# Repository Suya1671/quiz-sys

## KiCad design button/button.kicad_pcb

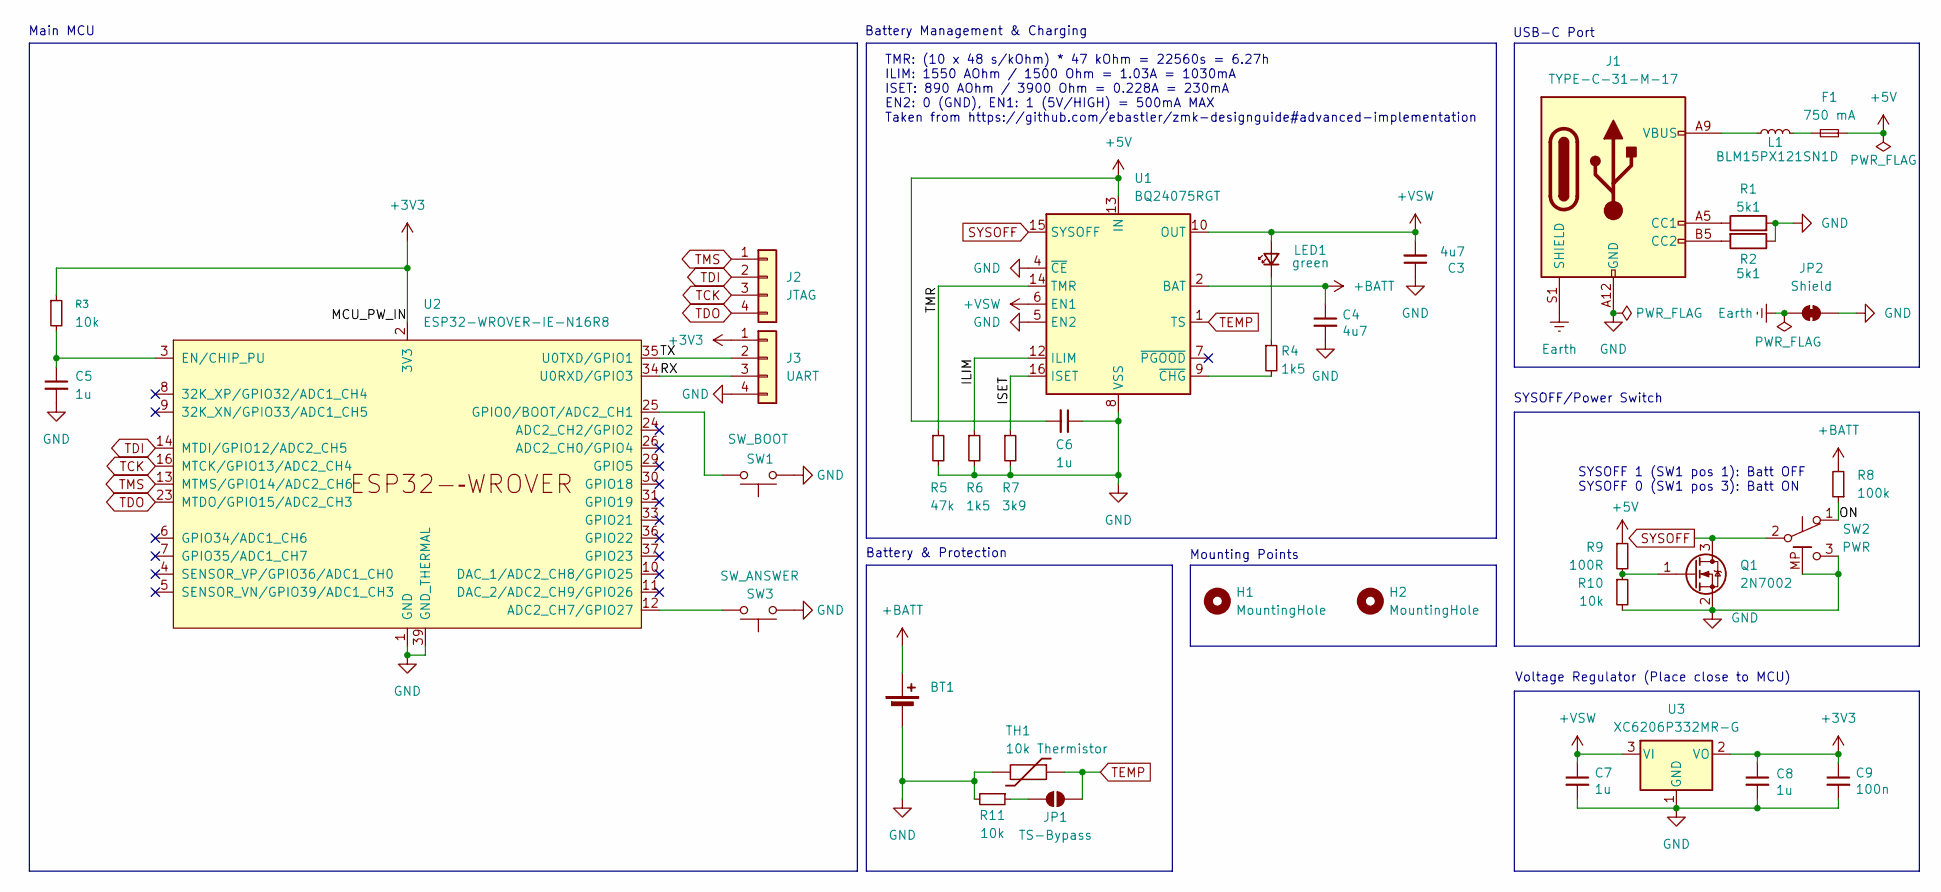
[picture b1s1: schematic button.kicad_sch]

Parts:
BT1: Battery_Cell; JST_PH_S2B-PH-K_1x02_P2.00mm_Horizontal
C3, C4: 4u7; C_0402_1005Metric_Pad0.74x0.62mm_HandSolder; LCSC C1538
C5, C6, C7, C8: 1u; C_0402_1005Metric_Pad0.74x0.62mm_HandSolder; LCSC C52923
C9: 100n; C_0402_1005Metric_Pad0.74x0.62mm_HandSolder; LCSC C1525
F1: 750 mA; Fuse_0603_1608Metric; LCSC C2687878
H1, H2: MountingHole; MountingHole_2.2mm_M2
J1: TYPE-C-31-M-17; USB_C_Receptacle_HRO_TYPE-C-31-M-17; LCSC C283540
J2: JTAG; PinHeader_1x04_P2.54mm_Horizontal; LCSC C91552
J3: UART; PinHeader_1x04_P2.54mm_Horizontal; LCSC C91552
JP1: TS-Bypass; SolderJumper-2_P1.3mm_Open_RoundedPad1.0x1.5mm
JP2: Shield; SolderJumper-2_P1.3mm_Bridged_RoundedPad1.0x1.5mm
L1: BLM15PX121SN1D; L_0402_1005Metric; LCSC C88970
LED1: green; LED_0603_1608Metric_Pad1.05x0.95mm_HandSolder; LCSC C2290
Q1: 2N7002; SOT-23; LCSC C8545
R1, R2: 5k1; R_0402_1005Metric_Pad0.72x0.64mm_HandSolder; LCSC C25905
R3, R10, R11: 10k; R_0402_1005Metric_Pad0.72x0.64mm_HandSolder; LCSC C25744
R4, R6: 1k5; R_0402_1005Metric_Pad0.72x0.64mm_HandSolder; LCSC C25867
R5: 47k; R_0402_1005Metric_Pad0.72x0.64mm_HandSolder; LCSC C25792
R7: 3k9; R_0603_1608Metric_Pad0.98x0.95mm_HandSolder; LCSC C23018
R8: 100k; R_0402_1005Metric_Pad0.72x0.64mm_HandSolder; LCSC C25741
R9: 100R; R_0402_1005Metric_Pad0.72x0.64mm_HandSolder; LCSC C25076
SW1: SW_BOOT; TS-1088-AR02016; LCSC C720477
SW2: PWR; SW_MSK12C02-HB; LCSC C431541
SW3: SW_ANSWER; WAGO 2060-452998-404; LCSC C2765055
TH1: 10k Thermistor; TestPoint_2Pads_Pitch5.08mm_Drill1.3mm
U1: BQ24075RGT; VQFN-16-1EP_3x3mm_P0.5mm_EP1.6x1.6mm; LCSC C15464
U2: ESP32-WROVER-IE-N16R8; ESP32-WROVER-E
U3: XC6206P332MR-G; SOT-23-3; LCSC C5446

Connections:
+3V3: C8.1, C9.1, J3.1, R3.1, U2.2 (3V3), U3.2 (VO)
+5V: C6.2, F1.2, R9.1, U1.13 (IN)
+BATT: BT1.1 (+), C4.1, R8.2, U1.2 (BAT), U1.3 (BAT)
+VSW: C3.2, C7.1, LED1.2 (A), U1.6 (EN1), U1.10 (OUT), U1.11 (OUT), U3.3 (VI)
/ILIM: R6.1, U1.12 (ILIM)
/ISET: R7.1, U1.16 (ISET)
/ON: R8.1, SW2.1 (A)
/RX: J3.3, U2.34 (U0RXD/GPIO3)
/TMR: R5.1, U1.14 (TMR)
/TX: J3.2, U2.35 (U0TXD/GPIO1)
Earth: J1.S1 (SHIELD), JP2.1 (A)
GND: BT1.2 (-), C3.1, C4.2, C5.2, C6.1, C7.2, C8.2, C9.2, J1.A12 (GND), J1.B12 (GND), J3.4, JP2.2 (B), Q1.2 (S), R1.2, R2.1, R5.2, R6.2, R7.2, R10.2, R11.2, SW1.1, SW2.3 (C), SW2.MP (Mounting), SW3.1, TH1.2, U1.4 (~CE), U1.5 (EN2), U1.8 (VSS), U1.17 (VSS), U2.1 (GND), U2.15 (GND), U2.38 (GND), U2.39 (GND_THERMAL), U3.1 (GND)
unnamed: F1.1, L1.2
unnamed: J1.A5 (CC1), R1.1
unnamed: J1.B5 (CC2), R2.2
unnamed: J1.A9 (VBUS), J1.B9 (VBUS), L1.1
unnamed: JP1.1 (A), R11.1
unnamed: LED1.1 (K), R4.1
unnamed: Q1.1 (G), R9.2, R10.1
unnamed: R4.2, U1.9 (~CHG)
unnamed: SW3.2, U2.12 (ADC2_CH7/GPIO27)
unnamed: C5.1, R3.2, U2.3 (EN/CHIP_PU)
unnamed: SW1.2, U2.25 (GPIO0/BOOT/ADC2_CH1)
SYSOFF: Q1.3 (D), SW2.2 (B), U1.15 (SYSOFF)
TCK: J2.3, U2.16 (MTCK/GPIO13/ADC2_CH4)
TDI: J2.2, U2.14 (MTDI/GPIO12/ADC2_CH5)
TDO: J2.4, U2.23 (MTDO/GPIO15/ADC2_CH3)
TEMP: JP1.2 (B), TH1.1, U1.1 (TS)
TMS: J2.1, U2.13 (MTMS/GPIO14/ADC2_CH6)

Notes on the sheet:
Mounting Points
USB-C Port
TMR: (10 x 48 s/kOhm) * 47 kOhm = 22560s = 6.27h ILIM: 1550 AOhm / 1500 Ohm = 1.03A = 1030mA ISET: 890 AOhm / 3900 Ohm = 0.228A = 230mA EN2: 0 (GND), EN1: 1 (5V/HIGH) = 500mA MAX Taken from https://github.com/ebastler/zmk-designguide#advanced-implementation
Battery Management & Charging
SYSOFF/Power Switch
Voltage Regulator (Place close to MCU)
Main MCU
SYSOFF 1 (SW1 pos 1): Batt OFF SYSOFF 0 (SW1 pos 3): Batt ON
Battery & Protection

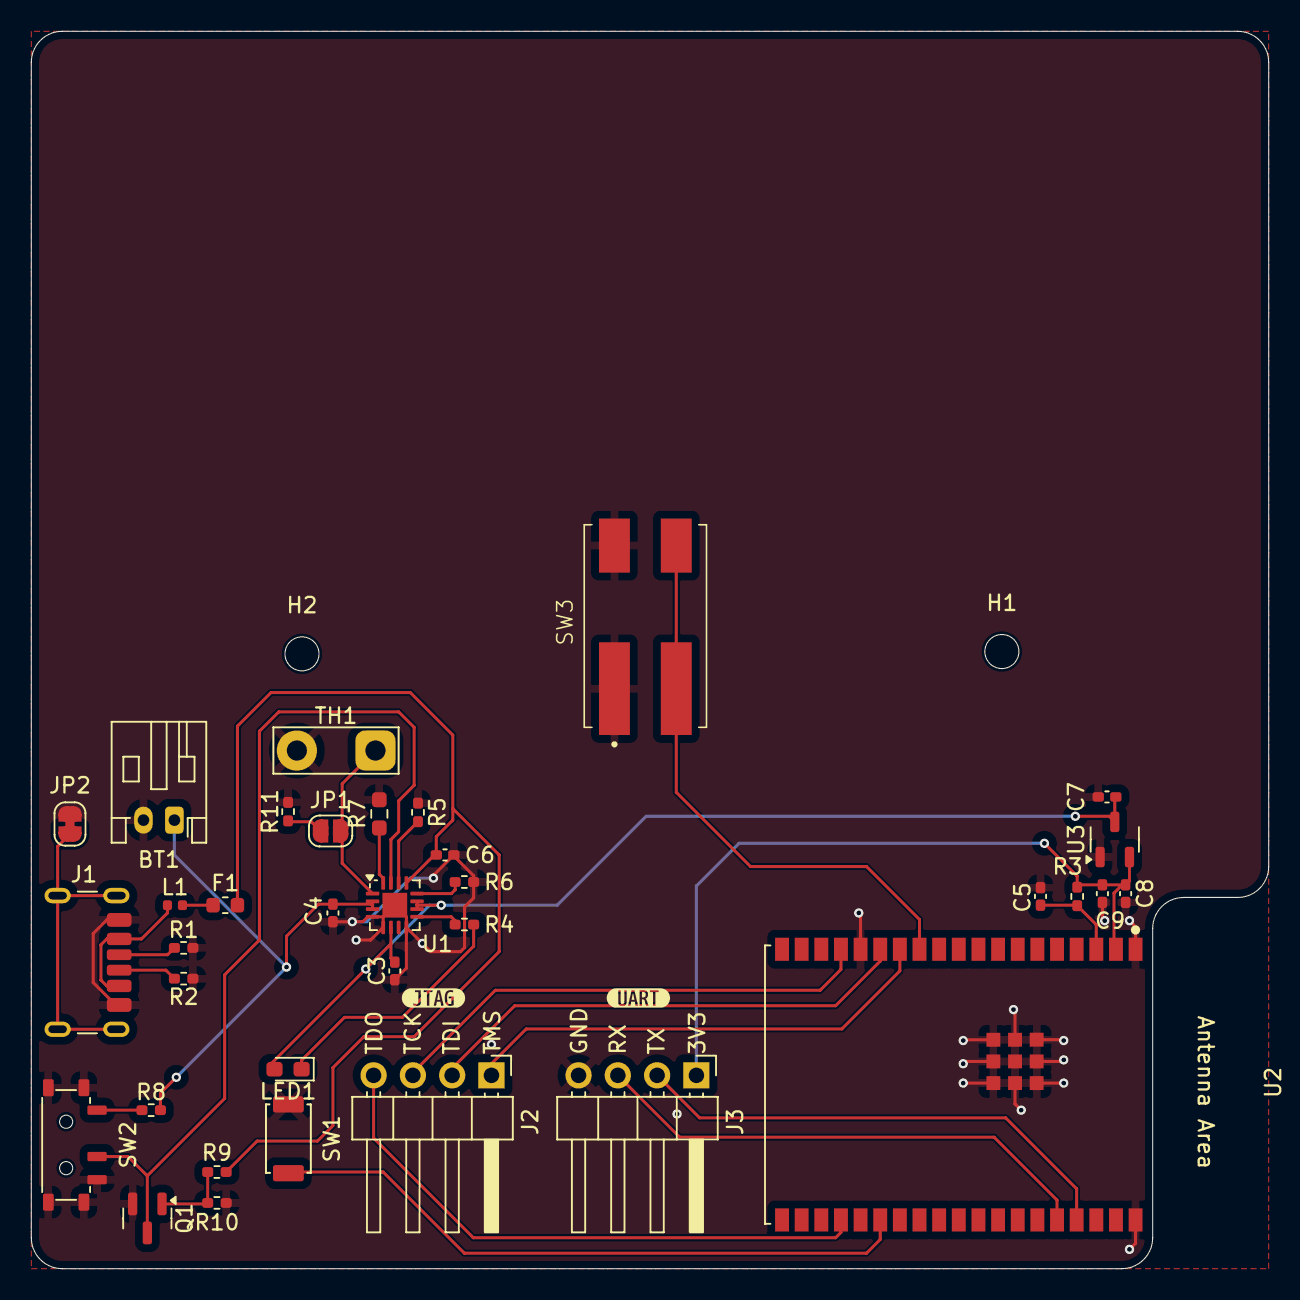
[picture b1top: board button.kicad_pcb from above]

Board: 2 copper layers, 80.0 x 80.0 mm, 39 parts (0 on the bottom side), 29 nets.

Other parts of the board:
kibuzzard-685930AE: G***; kibuzzard-685930AE
kibuzzard-6859309F: G***; kibuzzard-6859309F

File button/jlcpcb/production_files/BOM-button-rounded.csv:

Comment,Designator,Footprint,LCSC,Quantity
100n,C9,C_0402_1005Metric_Pad0.74x0.62mm_HandSolder,C1525,1
BQ24075RGT,U1,VQFN-16-1EP_3x3mm_P0.5mm_EP1.6x1.6mm,C15464,1
green,LED1,LED_0603_1608Metric_Pad1.05x0.95mm_HandSolder,C2290,1
3k9,R7,R_0603_1608Metric_Pad0.98x0.95mm_HandSolder,C23018,1
4u7,"C3,C4",C_0402_1005Metric_Pad0.74x0.62mm_HandSolder,C23733,2
100R,R9,R_0402_1005Metric_Pad0.72x0.64mm_HandSolder,C25076,1
100k,R8,R_0402_1005Metric_Pad0.72x0.64mm_HandSolder,C25741,1
10k,"R10,R11,R3",R_0402_1005Metric_Pad0.72x0.64mm_HandSolder,C25744,3
47k,R5,R_0402_1005Metric_Pad0.72x0.64mm_HandSolder,C25792,1
1k5,"R4,R6",R_0402_1005Metric_Pad0.72x0.64mm_HandSolder,C25867,2
5k1,"R1,R2",R_0402_1005Metric_Pad0.72x0.64mm_HandSolder,C25905,2
750 mA,F1,Fuse_0603_1608Metric,C2687878,1
SW_ANSWER,SW3,WAGO 2060-452998-404,C2765055,1
TYPE-C-31-M-17,J1,USB_C_Receptacle_HRO_TYPE-C-31-M-17,C283540,1
PWR,SW2,SW_MSK12C02-HB,C431541,1
1u,"C5,C6,C7,C8",C_0402_1005Metric_Pad0.74x0.62mm_HandSolder,C52923,4
XC6206P332MR-G,U3,SOT-23-3,C5446,1
SW_BOOT,SW1,TS-1088-AR02016,C720477,1
2N7002,Q1,SOT-23,C8545,1
BLM15PX121SN1D,L1,L_0402_1005Metric,C88970,1
JTAG,"J2,J3",PinHeader_1x04_P2.54mm_Horizontal,C91552,2

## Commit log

2025-07-04 feat: initial commit
